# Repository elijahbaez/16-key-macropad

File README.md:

# ⌨️ Custom 16-Key Mechanical Macropad

A custom-built, programmable 16-key mechanical macropad powered by an RP2040 microcontroller. Designed to streamline custom PC building operations by automating hardware-level system-testing workflows, replacing repetitive manual data entry with a dedicated hardware interface.

## ✨ Features

* **Anti-Ghosting Matrix:** Features a custom 4x4 switch matrix with a 1N4148 diode array to completely eliminate key ghosting.
* **Isolated 2-Layer Routing:** Routed using 2-layer traces in KiCad, deliberately isolating horizontal rows on the bottom copper layer (blue) and vertical columns on the top copper layer (red) for optimal signal integrity.
* **Hardware Automation:** Programmed with 3 dedicated macro layers in C++ utilizing QMK's `process_record_user` state machine.
* **Workflow Integration:** Automates redundant PC system-testing workflows (launching hardware telemetry/sensors, automated network ping tests, and instant task manager overrides).

## 🗂️ Project Structure & Configuration

### Repository Layout
* **/macropad** — Contains the KiCad hardware schematic, PCB layout (`.kicad_pcb`), and footprint files.
* **/firmware** — Contains the C++ QMK environment, hardware configurations (`info.json`), and the macro logic (`keymap.c`).

### C++ Macro Implementation

---

> ### 📋 Technical Notes on QMK Implementation
> The macropad utilizes a `COL2ROW` diode direction configuration mapped directly to the RP2040's GPIO pins. The macro implementation leverages QMK's `SEND_STRING` functionality combined with `SS_DELAY` to account for OS-level execution latency when automating command-prompt-based benchmarking tools. 
> 
> The hardware matrix prevents electrical shorts by keeping column/row polling strictly on independent planes (Front Copper and Back Copper).

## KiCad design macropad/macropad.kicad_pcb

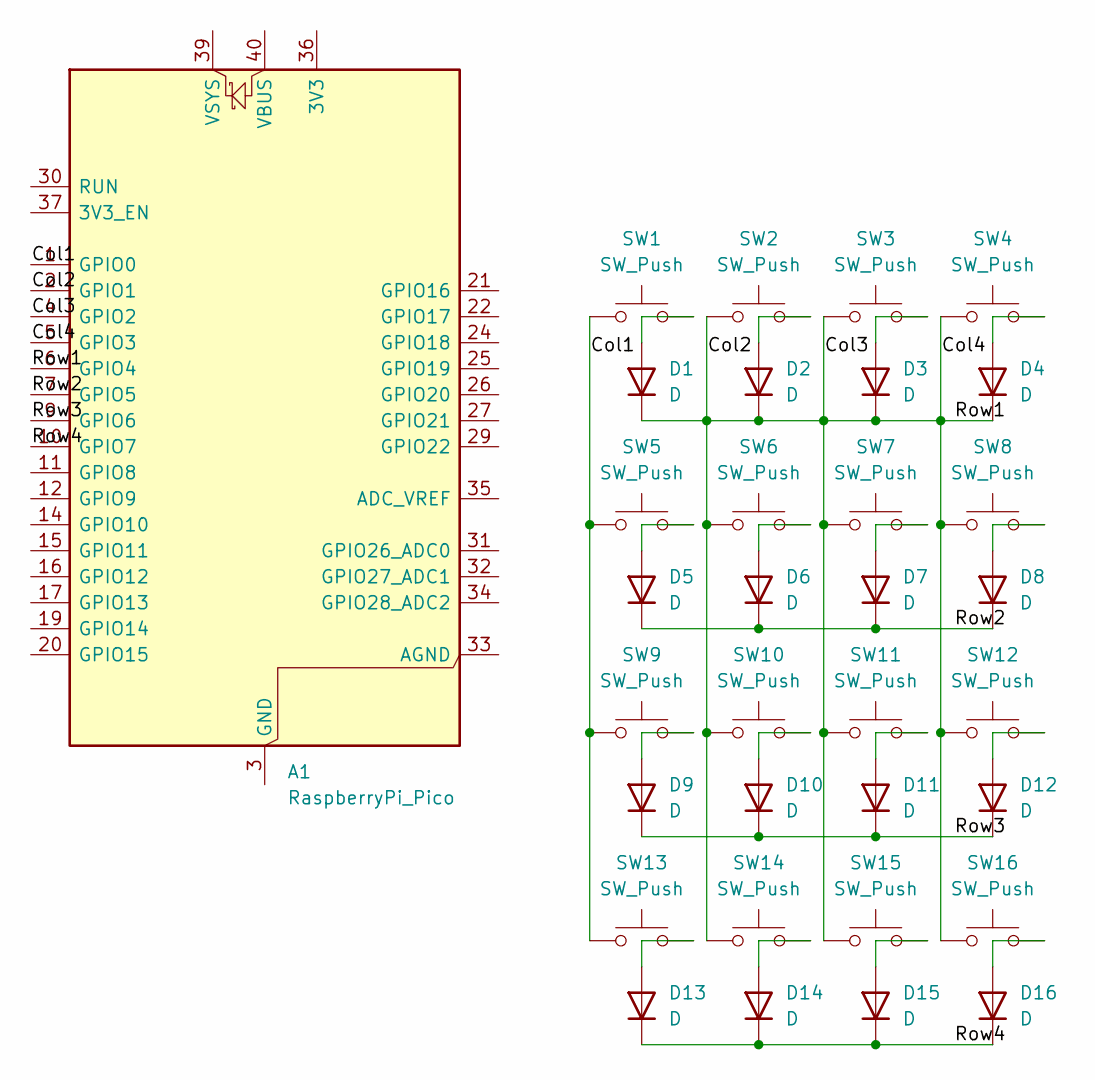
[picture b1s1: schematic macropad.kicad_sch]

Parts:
A1: RaspberryPi_Pico; RaspberryPi_Pico_Common_THT
D1, D2, D3, D4, D5, D6, D7, D8, D9, D10, D11, D12, D13, D14, D15, D16: D; D_DO-35_SOD27_P7.62mm_Horizontal
SW1, SW2, SW3, SW4, SW5, SW6, SW7, SW8, SW9, SW10, SW11, SW12, SW13, SW14, SW15, SW16: SW_Push; SW_Cherry_MX_1.00u_PCB

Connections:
/Col1: A1.1 (GPIO0), SW1.1, SW5.1, SW9.1, SW13.1
/Col2: A1.2 (GPIO1), A1.4 (GPIO2), A1.5 (GPIO3), A1.6 (GPIO4), D1.1 (K), D2.1 (K), D3.1 (K), D4.1 (K), SW2.1, SW3.1, SW4.1, SW6.1, SW7.1, SW8.1, SW10.1, SW11.1, SW12.1, SW14.1, SW15.1, SW16.1
/Row2: A1.7 (GPIO5), D5.1 (K), D6.1 (K), D7.1 (K), D8.1 (K)
/Row3: A1.9 (GPIO6), D9.1 (K), D10.1 (K), D11.1 (K), D12.1 (K)
/Row4: A1.10 (GPIO7), D13.1 (K), D14.1 (K), D15.1 (K), D16.1 (K)
unnamed: A1.3 (GND), A1.8 (GND), A1.13 (GND), A1.18 (GND), A1.23 (GND), A1.28 (GND), A1.38 (GND)
unnamed: D1.2 (A), SW1.2
unnamed: D2.2 (A), SW2.2
unnamed: D3.2 (A), SW3.2
unnamed: D4.2 (A), SW4.2
unnamed: D5.2 (A), SW5.2
unnamed: D6.2 (A), SW6.2
unnamed: D7.2 (A), SW7.2
unnamed: D8.2 (A), SW8.2
unnamed: D9.2 (A), SW9.2
unnamed: D10.2 (A), SW10.2
unnamed: D11.2 (A), SW11.2
unnamed: D12.2 (A), SW12.2
unnamed: D13.2 (A), SW13.2
unnamed: D14.2 (A), SW14.2
unnamed: D15.2 (A), SW15.2
unnamed: D16.2 (A), SW16.2

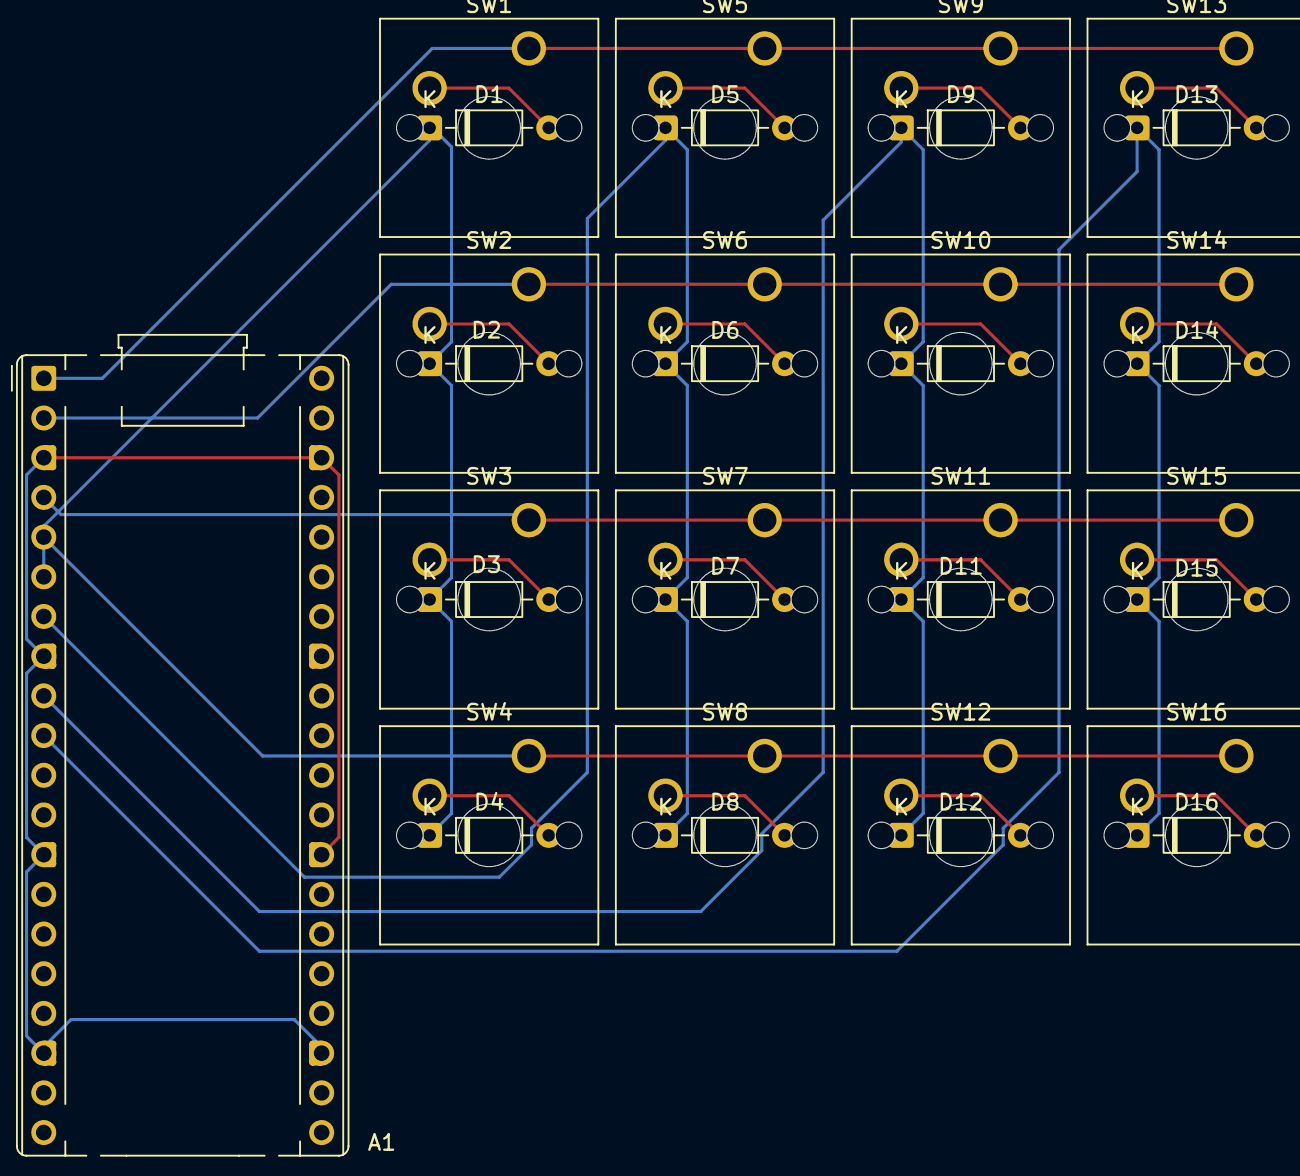
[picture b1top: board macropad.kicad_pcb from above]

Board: 2 copper layers, 33 parts (0 on the bottom side), 22 nets.
